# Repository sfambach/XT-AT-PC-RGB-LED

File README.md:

# XT-AT-PC-RGB-LED

**One RGB LED instead of separate power, turbo and HDD LEDs for retro PCs (XT / AT)**

| State | Colour |
|---|---|
| Power on | green |
| Turbo on | red (instead of green) |
| HDD activity | blue, overrides green and red |

It plugs into the normal mainboard headers (power LED, HDD LED, turbo LED). Two NPN transistors, five small diodes and two resistors, through-hole parts only, powered from the power LED header.

**Status: concept, simulated (ngspice).** Not built or tested yet.

## How it works

- Common anode of the RGB LED is fed from `PLED+`. The mainboard's own series resistor sets the current (optional R0 if the board has none).
- Blue cathode goes straight to `HDD-`. The open-collector HDD driver pulls it low on activity, exactly like the original HDD LED.
- Green: Q1 switches the green cathode to GND. R1 keeps Q1 on. D1 (from `HDD-`) or D2 (from `TURBO-`) pull its base down and turn green off. D4 in the emitter lifts the turn-on threshold above that one diode drop.
- Red: Q2 switches the red cathode to `TURBO-`, so red can only light while turbo is active. D3 pulls its base down on HDD activity, D5 again lifts the threshold.
- The diodes keep the two inputs apart: no input leaks into the other colour.
- `HDD+` and `TURBO+` are not used. Without a turbo connection leave out Q2, R2, D3 and D5.

Details, variants and simulation results: [docs/concept.md](docs/concept.md)

## Versions

| Version | What | Status |
|---|---|---|
| **v1** | discrete, no microcontroller, through-hole board ([hardware/v1](hardware/v1)) | simulated, board designed |
| **v2** | ATtiny84 board for an addressable LED and/or a plain RGB LED or RGB button, colours from a config file, no measuring of the headers needed ([v2/](v2/README.md), [hardware/v2](hardware/v2)) | firmware compiled, board designed |
| v3 | full SMD version | planned |

Simulation (ngspice): [sim/](sim/), transient plot `sim/three_states_tran.png`.

## History and key points

The project started as "one RGB LED for power and HDD" and grew step by step:

1. **Power + HDD with one LED.** A single diode in series with green only works with InGaN green LEDs: with a common anode the colour with the lowest forward voltage wins. One transistor solves it.
2. **Turbo added (red).** Red has about 2 V forward voltage and pulls the common anode down, so mixing colours (yellow) does not work. Result: two transistors, five diodes, HDD has priority (v1).
3. **Unknown header polarity.** Which pin of the turbo header switches is not standardised. Instead of measuring every board, v2 uses a load resistor between the two pins and treats "pins differ" as active.
4. **Microcontroller (v2).** A logic IC was rejected for v1 because the front panel has no clean 5 V. v2 accepts an extra 5 V cable and gets colours from a config file.
5. **Addressable or plain RGB?** Addressable LEDs need no resistors and can be chained; illuminated RGB buttons only exist as plain RGB. v2 has both outputs, so the power button itself can be the indicator.
6. **Boards.** v1 and v2 through-hole with the common M3 hole rule; v3 (full SMD) is planned.

Open: measurement of the front panel headers, 5 V source for v2, building and testing.

## Parts

| Ref | Part | Note |
|---|---|---|
| R1, R2 | 10 kΩ, 1/4 W | base resistors |
| R0 | 330 Ω, 1/4 W | only if `PLED+` has no series resistor on the board, otherwise bridge |
| Q1, Q2 | BC547B (BC548, 2N3904 also fine) | |
| D1–D5 | 1N4148 | |
| LED1 | RGB LED 5 mm, common anode, diffused, 4 pins | 3 mm also fine |

## License

- Hardware: [CERN-OHL-S-2.0](LICENSE)
- Firmware and tools (v2): PolyForm Noncommercial 1.0.0, see [v2/LICENSE.md](v2/LICENSE.md)
- Documentation: CC BY-SA 4.0

## Authors

- **Stefan Fambach** (SteFam) – idea and concept, review and testing – https://www.fambach.net
- **Claude** (Anthropic AI) – implementation, via Claude Code

## AI disclosure

This project is built with AI assistance. Stefan Fambach had the idea, wrote the concept and reviews and tests every change; the implementation (schematics, simulation, firmware and documentation) is written largely by Claude (Anthropic) via Claude Code.

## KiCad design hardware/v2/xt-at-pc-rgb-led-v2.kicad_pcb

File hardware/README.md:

# Hardware

Two small through-hole boards, generated with KiCad 7 from Python scripts (`generator/`) and routed with Freerouting.

| Board | Size | Content |
|---|---|---|
| [v1](v1/) | 44 × 26.5 mm | discrete: 2× BC547, 5× 1N4148, 3 resistors |
| [v2](v2/) | 42 × 40.4 mm | ATtiny84 in a DIP-14 socket, 6-pin AVR ISP, addressable and plain RGB LED output |

Each folder has the KiCad project, schematic PDF, Gerber ZIP, DRC report and top/bottom renders. 2D dimension drawings (top, front and side view) are in [drawings/](drawings/), generated from the PCB by `generator/drawing.py`.

**Status: not manufactured, not tested.** DRC: 0 unconnected pads, only silkscreen overlaps left.

## Common rules

- **Mounting:** two M3 holes (3.2 mm) on the long axis, centred, 3.5 mm from the short edges – the same on every board.
- **Connectors:** 2.54 mm pin headers. Front panel headers are 1×2 with pin 1 = `+`, pin 2 = `-`, so the usual 2-pin case cables fit.
- **LED** on a cable (1×4 header), so the board can sit anywhere behind the front panel.
- **Button / switch:** `SW IN` and `SW OUT` are connected 1:1 (pass-through only, no electronics).

## Dimensions

| Board | Outline | Holes (from top left corner) |
|---|---|---|
| v1 | 44 × 26.5 × 1.6 mm | Ø3.2 at (3.5 / 13.25) and (40.5 / 13.25) |
| v2 | 42 × 40.4 × 1.6 mm | Ø3.2 at (3.5 / 20.2) and (38.5 / 20.2) |

Resistors and diodes lie flat (7.62 mm pitch, side by side). Assumed, not measured: about 8.5 mm component height above the board (pin headers, DIP socket, TO-92) and about 3 mm leads below. Angled headers change the height.

The mounting holes sit in gaps between the parts instead of outside them, which keeps the boards narrow.

## v1 connectors

| Ref | Pins | Function |
|---|---|---|
| J1 | PLED + / − | supply (power LED header) |
| J2 | HDD + / − | only `−` is used |
| J3 | TURBO + / − | only `−` is used |
| J4 | A R G B | RGB LED, common anode |
| J5 / J6 | SW IN / SW OUT | pass-through |

R0 only if `PLED+` has no series resistor on the mainboard, otherwise a wire bridge.

## v2 connectors

| Ref | Pins | Function |
|---|---|---|
| J1 | +5V GND | supply (speaker header / floppy connector, to be checked) |
| J2 / J3 | HDD, TURBO | any polarity, R1/R4 4.7 kΩ load between the pins |
| J4 / J5 | SW IN / SW OUT | pass-through |
| J6 | 5V DATA GND | addressable LED |
| J7 | COM R G B | plain RGB LED / RGB button, R9–R11 only when used |
| JP1 | A – COM – K | COM to +5 V (common anode) or GND (common cathode) |
| J8 | ISP | standard 6-pin AVR ISP (MISO VCC / SCK MOSI / RST GND) |

The ATtiny84 can also be programmed in a socket programmer (XGecu T48). MOSI is shared with the blue PWM output; the blue LED may flicker while programming.

## Rebuild

```
cd generator
FREEROUTING=/path/to/freerouting-1.9.0.jar sh build.sh v1
sh outputs.sh v1
```

Freerouting is not deterministic; if the DRC reports unconnected pads, run `build.sh` again.

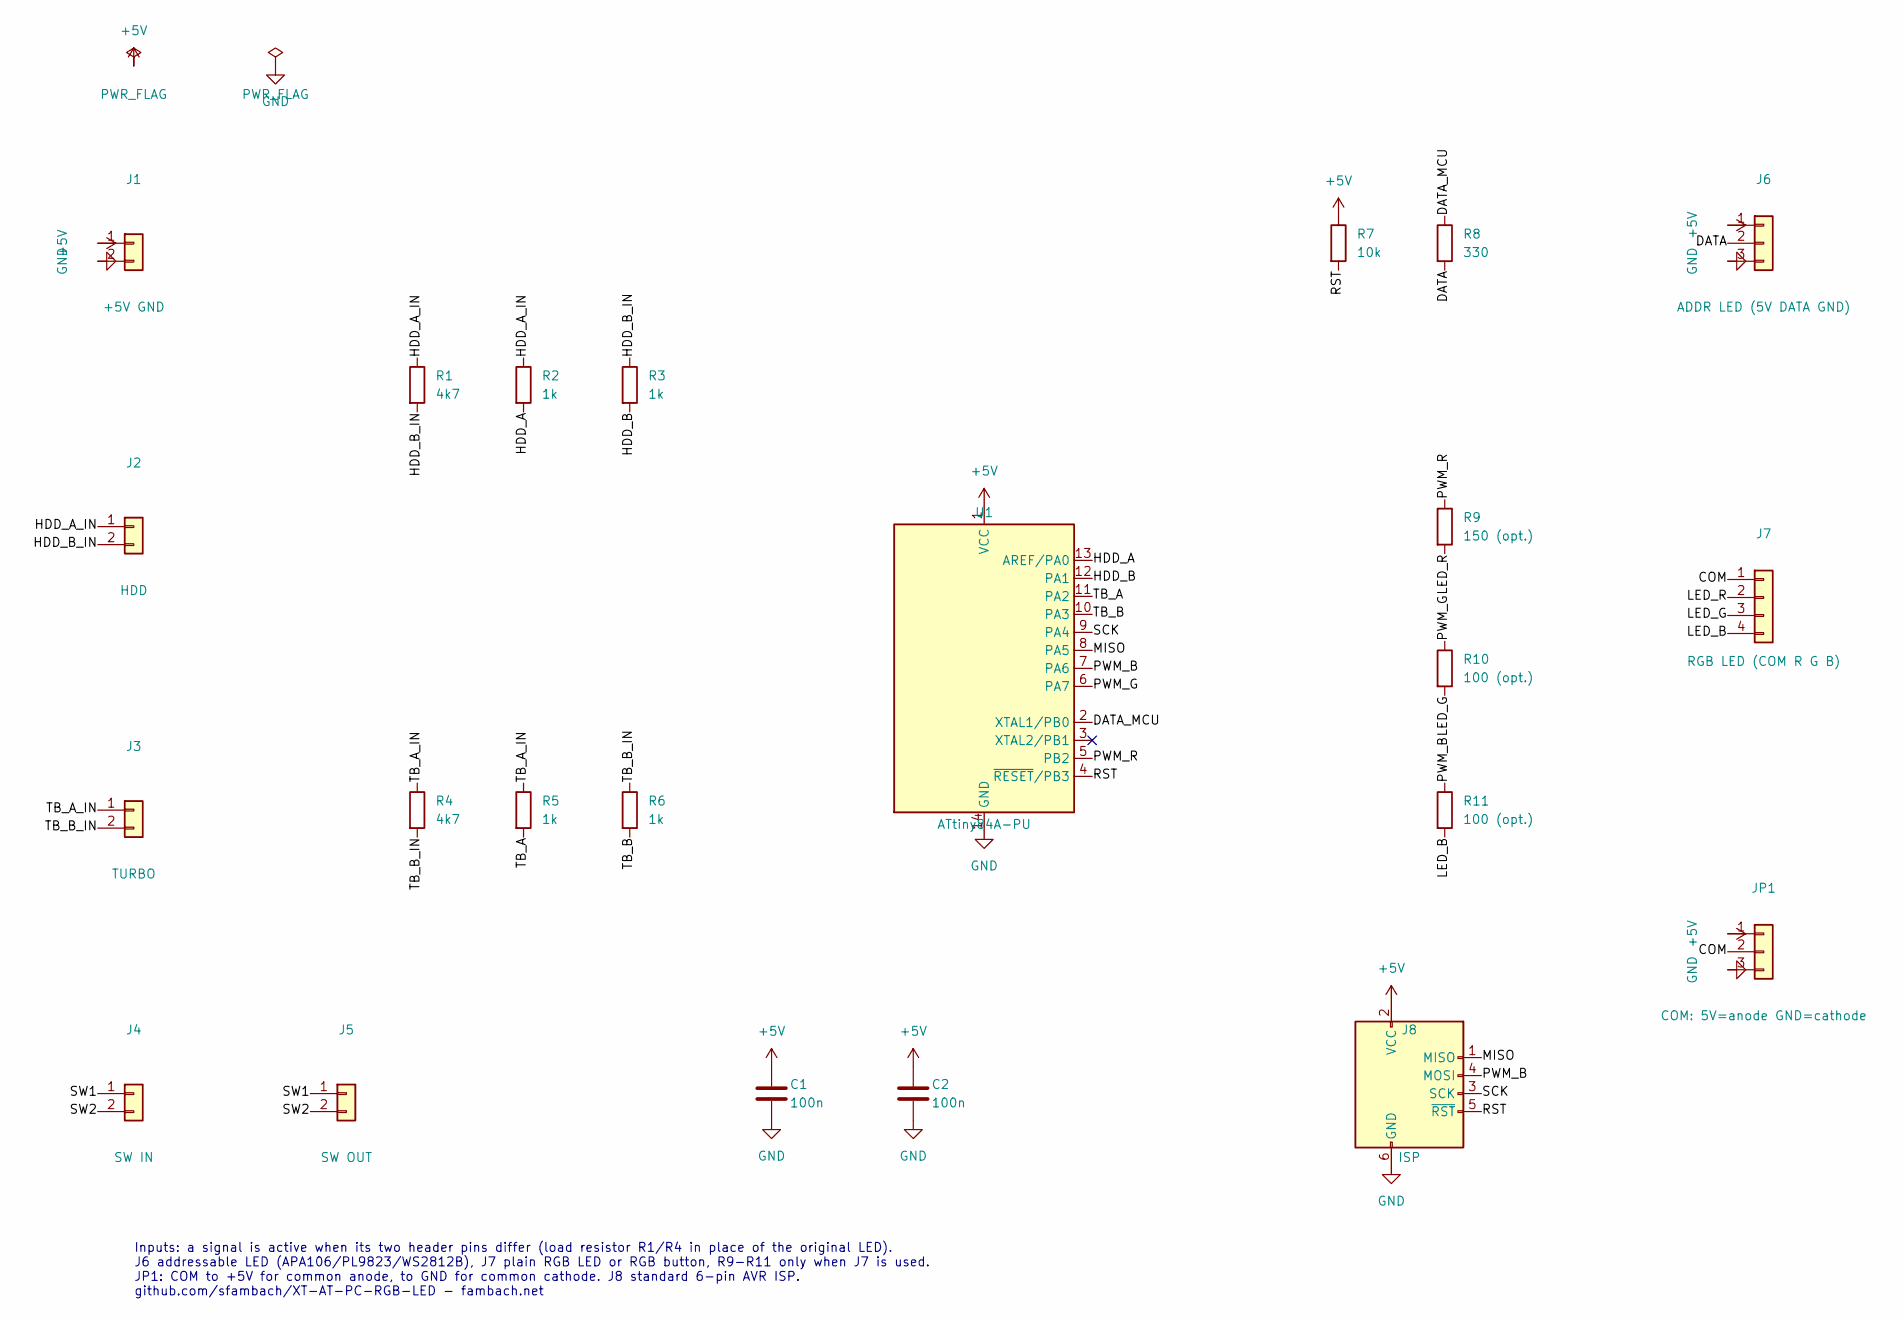
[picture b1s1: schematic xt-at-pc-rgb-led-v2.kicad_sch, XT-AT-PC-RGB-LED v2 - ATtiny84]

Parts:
C1, C2: 100n; C_Disc_D3.0mm_W1.6mm_P2.50mm
J1: +5V GND; PinHeader_1x02_P2.54mm_Vertical
J2: HDD; PinHeader_1x02_P2.54mm_Vertical
J3: TURBO; PinHeader_1x02_P2.54mm_Vertical
J4: SW IN; PinHeader_1x02_P2.54mm_Vertical
J5: SW OUT; PinHeader_1x02_P2.54mm_Vertical
J6: ADDR LED (5V DATA GND); PinHeader_1x03_P2.54mm_Vertical
J7: RGB LED (COM R G B); PinHeader_1x04_P2.54mm_Vertical
J8: ISP; PinHeader_2x03_P2.54mm_Vertical
JP1: COM: 5V=anode GND=cathode; PinHeader_1x03_P2.54mm_Vertical
R1, R4: 4k7; R_Axial_DIN0207_L6.3mm_D2.5mm_P7.62mm_Horizontal
R2, R3, R5, R6: 1k; R_Axial_DIN0207_L6.3mm_D2.5mm_P7.62mm_Horizontal
R7: 10k; R_Axial_DIN0207_L6.3mm_D2.5mm_P7.62mm_Horizontal
R8: 330; R_Axial_DIN0207_L6.3mm_D2.5mm_P7.62mm_Horizontal
R9: 150 (opt.); R_Axial_DIN0207_L6.3mm_D2.5mm_P7.62mm_Horizontal
R10, R11: 100 (opt.); R_Axial_DIN0207_L6.3mm_D2.5mm_P7.62mm_Horizontal
U1: ATtiny84A-PU; DIP-14_W7.62mm_Socket

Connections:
+5V: C1.1, C2.1, J1.1, J6.1, J8.2 (VCC), JP1.1, R7.1, U1.1 (VCC)
/COM: J7.1, JP1.2
/DATA: J6.2, R8.2
/DATA_MCU: R8.1, U1.2 (XTAL1/PB0)
/HDD_A: R2.2, U1.13 (AREF/PA0)
/HDD_A_IN: J2.1, R1.1, R2.1
/HDD_B: R3.2, U1.12 (PA1)
/HDD_B_IN: J2.2, R1.2, R3.1
/LED_B: J7.4, R11.2
/LED_G: J7.3, R10.2
/LED_R: J7.2, R9.2
/MISO: J8.1 (MISO), U1.8 (PA5)
/PWM_B: J8.4 (MOSI), R11.1, U1.7 (PA6)
/PWM_G: R10.1, U1.6 (PA7)
/PWM_R: R9.1, U1.5 (PB2)
/RST: J8.5 (~RST), R7.2, U1.4 (~RESET/PB3)
/SCK: J8.3 (SCK), U1.9 (PA4)
/SW1: J4.1, J5.1
/SW2: J4.2, J5.2
/TB_A: R5.2, U1.11 (PA2)
/TB_A_IN: J3.1, R4.1, R5.1
/TB_B: R6.2, U1.10 (PA3)
/TB_B_IN: J3.2, R4.2, R6.1
GND: C1.2, C2.2, J1.2, J6.3, J8.6 (GND), JP1.3, U1.14 (GND)

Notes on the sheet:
Inputs: a signal is active when its two header pins differ (load resistor R1/R4 in place of the original LED). J6 addressable LED (APA106/PL9823/WS2812B), J7 plain RGB LED or RGB button, R9-R11 only when J7 is used. JP1: COM to +5V for common anode, to GND for common cathode. J8 standard 6-pin AVR 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

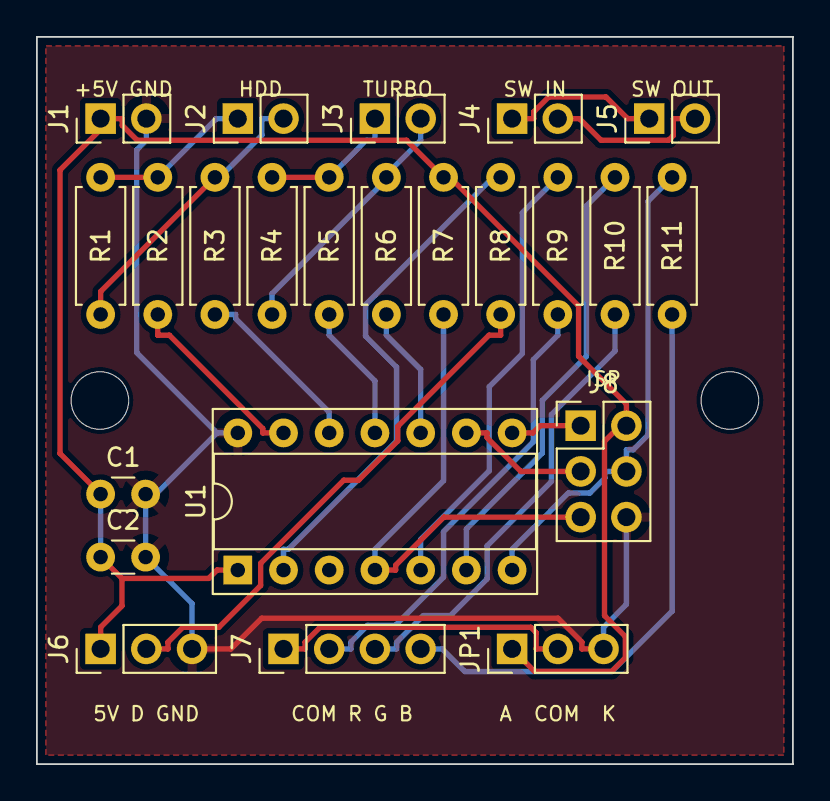
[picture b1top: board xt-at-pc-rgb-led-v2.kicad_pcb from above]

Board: 2 copper layers, 42.0 x 40.4 mm, 25 parts (0 on the bottom side), 24 nets.

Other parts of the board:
H1, H2: M3; MountingHole_3.2mm_M3

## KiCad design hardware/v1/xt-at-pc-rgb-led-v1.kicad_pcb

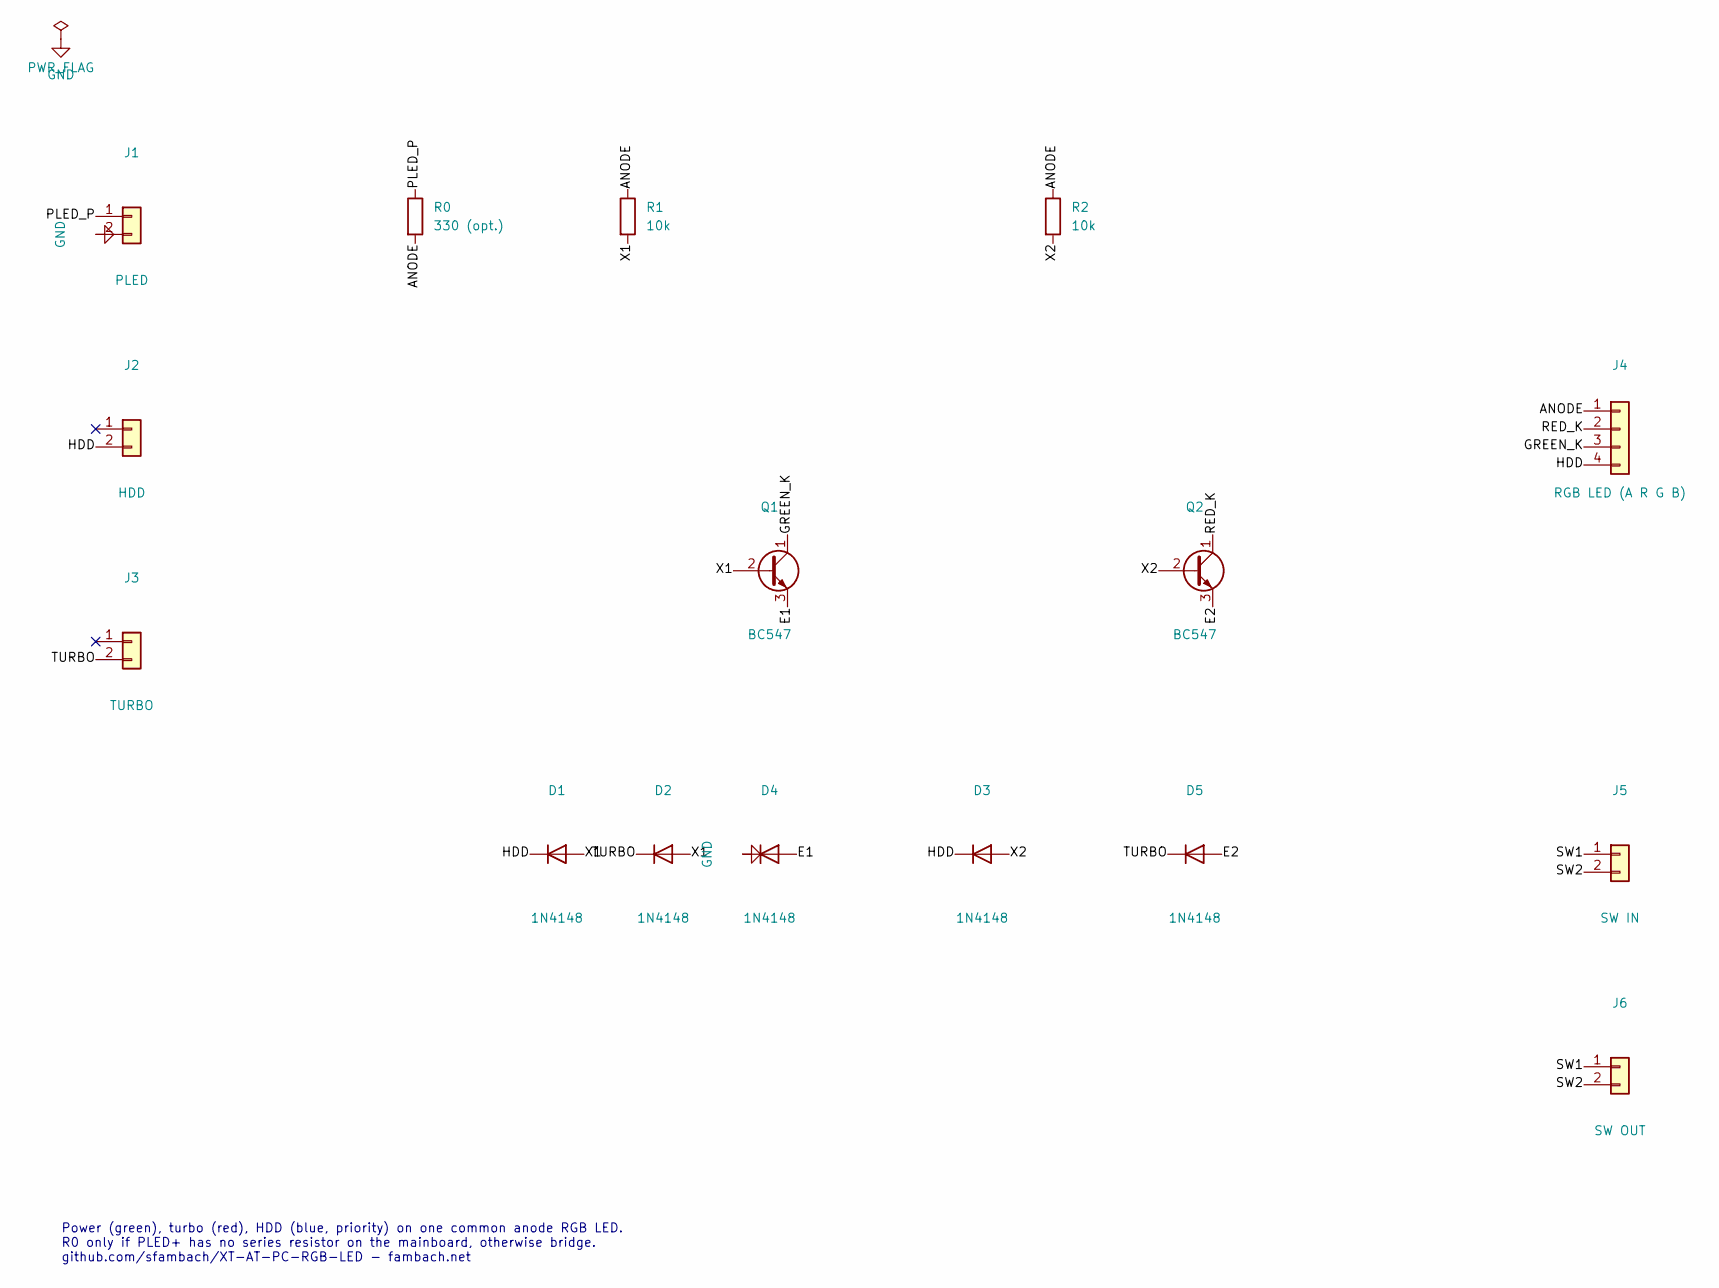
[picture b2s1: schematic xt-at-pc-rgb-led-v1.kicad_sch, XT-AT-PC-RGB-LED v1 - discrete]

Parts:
D1, D2, D3, D4, D5: 1N4148; D_DO-35_SOD27_P7.62mm_Horizontal
J1: PLED; PinHeader_1x02_P2.54mm_Vertical
J2: HDD; PinHeader_1x02_P2.54mm_Vertical
J3: TURBO; PinHeader_1x02_P2.54mm_Vertical
J4: RGB LED (A R G B); PinHeader_1x04_P2.54mm_Vertical
J5: SW IN; PinHeader_1x02_P2.54mm_Vertical
J6: SW OUT; PinHeader_1x02_P2.54mm_Vertical
Q1, Q2: BC547; TO-92_Inline_Wide
R0: 330 (opt.); R_Axial_DIN0207_L6.3mm_D2.5mm_P7.62mm_Horizontal
R1, R2: 10k; R_Axial_DIN0207_L6.3mm_D2.5mm_P7.62mm_Horizontal

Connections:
/ANODE: J4.1, R0.2, R1.1, R2.1
/E1: D4.2 (A), Q1.3 (E)
/E2: D5.2 (A), Q2.3 (E)
/GREEN_K: J4.3, Q1.1 (C)
/HDD: D1.1 (K), D3.1 (K), J2.2, J4.4
/PLED_P: J1.1, R0.1
/RED_K: J4.2, Q2.1 (C)
/SW1: J5.1, J6.1
/SW2: J5.2, J6.2
/TURBO: D2.1 (K), D5.1 (K), J3.2
/X1: D1.2 (A), D2.2 (A), Q1.2 (B), R1.2
/X2: D3.2 (A), Q2.2 (B), R2.2
GND: D4.1 (K), J1.2

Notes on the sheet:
Power (green), turbo (red), HDD (blue, priority) on one common anode RGB LED. R0 only if PLED+ has no series resistor on the mainboard, otherwise bridge. github.com/sfambach/XT-AT-PC-RGB-LED - fambach.net

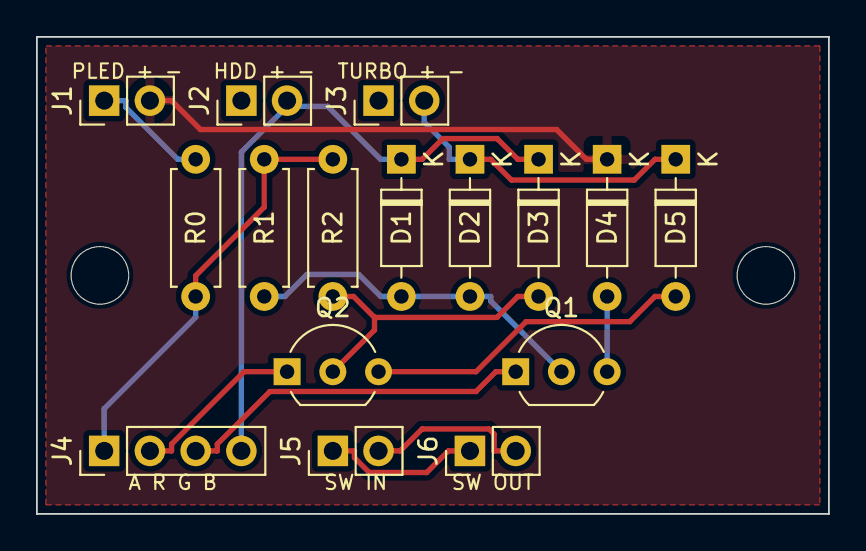
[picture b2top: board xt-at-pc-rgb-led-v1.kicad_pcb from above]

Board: 2 copper layers, 44.0 x 26.5 mm, 18 parts (0 on the bottom side), 13 nets.

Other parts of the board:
H1, H2: M3; MountingHole_3.2mm_M3

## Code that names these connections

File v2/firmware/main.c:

/*
 * XT-AT-PC-RGB-LED v2 - one RGB LED for power, turbo and HDD
 * Copyright (C) 2026 Stefan Fambach (SteFam), https://www.fambach.net
 * License: PolyForm Noncommercial 1.0.0, see ../LICENSE.md
 *
 * Internal oscillator: ATtiny84 / ATtiny85 @ 8 MHz, ATtiny13A @ 9.6 MHz.
 *
 * ATtiny85 / ATtiny13A (addressable LED only)
 *   PB0 LED data   PB1/PB2 HDD header pins A/B   PB3/PB4 TURBO header pins A/B
 *
 * ATtiny84 (addressable LED and plain RGB LED at the same time)
 *   PB0 LED data   PA0/PA1 HDD header pins A/B   PA2/PA3 TURBO header pins A/B
 *   PB2 (OC0A) red   PA7 (OC0B) green   PA6 (OC1A) blue
 *
 * Each header gets a load resistor between its two pins. A signal is active
 * when its two pins differ, so neither the header polarity nor the switching
 * side (low or high) has to be known in advance.
 */
#include <avr/io.h>
#include <avr/eeprom.h>
#include <avr/interrupt.h>
#include <util/delay.h>
#include "config.h"

#define LED_BIT    _BV(PB0)
#define REFRESH_MS 500

#if defined(__AVR_ATtiny84__) || defined(__AVR_ATtiny84A__)
#define HAS_RGB_OUTPUT 1
#define INPUT_PIN  PINA
#define INPUT_PORT PORTA
#define HDD_A PA0
#define HDD_B PA1
#define TURBO_A PA2
#define TURBO_B PA3
#else
#define HAS_RGB_OUTPUT 0
#define INPUT_PIN  PINB
#define INPUT_PORT PORTB
#define HDD_A PB1
#define HDD_B PB2
#define TURBO_A PB3
#define TURBO_B PB4
#endif
#define INPUTS (_BV(HDD_A) | _BV(HDD_B) | _BV(TURBO_A) | _BV(TURBO_B))

static struct config cfg;

/* 11 cycles per bit: high 3 cycles for 0, 7 cycles for 1 (8 / 9.6 MHz). */
static void send_byte(uint8_t value, uint8_t hi, uint8_t lo)
{
    uint8_t count = 8;
    __asm__ volatile(
        "1:                 \n\t"
        "out  %[port], %[hi]\n\t"
        "nop                \n\t"
        "sbrs %[val], 7     \n\t"
        "out  %[port], %[lo]\n\t"
        "lsl  %[val]        \n\t"
        "nop                \n\t"
        "nop                \n\t"
        "out  %[port], %[lo]\n\t"
        "dec  %[cnt]        \n\t"
        "brne 1b            \n\t"
        : [val] "+r"(value), [cnt] "+r"(count)
        : [port] "I"(_SFR_IO_ADDR(PORTB)), [hi] "r"(hi), [lo] "r"(lo));
}

static uint8_t scale(uint8_t channel)
{
    return (uint16_t)channel * (cfg.brightness + 1) >> 8;
}

#if HAS_RGB_OUTPUT
/*
 * Hardware PWM, 8 bit, ~3.9 kHz. Common anode is driven inverted (low = on).
 * A channel at 0 is disconnected from the timer and held at its off level,
 * because fast PWM never reaches a duty of exactly 0.
 */
static void pwm_init(void)
{
    if (cfg.rgb_output == RGB_NONE)
        return;
    if (cfg.rgb_output == RGB_COMMON_ANODE) {
        PORTB |= _BV(PB2);
        PORTA |= _BV(PA7) | _BV(PA6);
    }
    DDRB |= _BV(PB2);
    DDRA |= _BV(PA7) | _BV(PA6);
    TCCR0A = _BV(WGM01) | _BV(WGM00);
    TCCR0B = _BV(CS01);
    TCCR1A = _BV(WGM10);
    TCCR1B = _BV(WGM12) | _BV(CS11);
}

static uint8_t com_bits(uint8_t value, uint8_t com1, uint8_t com0)
{
    if (value == 0)
        return 0;
    return cfg.rgb_output == RGB_COMMON_ANODE ? (com1 | com0) : com1;
}

static void pwm_show(uint8_t r, uint8_t g, uint8_t b)
{
    if (cfg.rgb_output == RGB_NONE)
        return;
    OCR0A = r - 1;
    OCR0B = g - 1;
    OCR1A = b - 1;
    TCCR0A = _BV(WGM01) | _BV(WGM00) |
             com_bits(r, _BV(COM0A1), _BV(COM0A0)) |
             com_bits(g, _BV(COM0B1), _BV(COM0B0));
    TCCR1A = _BV(WGM10) | com_bits(b, _BV(COM1A1), _BV(COM1A0));
}
#endif

static void show(const uint8_t rgb[3])
{
    uint8_t r = scale(rgb[0]), g = scale(rgb[1]), b = scale(rgb[2]);
    uint8_t first = cfg.order == ORDER_RGB ? r : g;
    uint8_t second = cfg.order == ORDER_RGB ? g : r;
    uint8_t hi = PORTB | LED_BIT, lo = PORTB & ~LED_BIT;

    cli();
    for (uint8_t i = 0; i < cfg.led_count; i++) {
        send_byte(first, hi, lo);
        send_byte(second, hi, lo);
        send_byte(b, hi, lo);
    }
    sei();
#if HAS_RGB_OUTPUT
    pwm_show(r, g, b);
#endif
    _delay_us(80); /* latch */
}

static void load_config(void)
{
    static const struct config defaults = CONFIG_DEFAULTS;

    eeprom_read_block(&cfg, 0, sizeof cfg);
    if (cfg.magic != CONFIG_MAGIC || cfg.version != CONFIG_VERSION || cfg.led_count == 0)
        cfg = defaults;
}

int main(void)
{
    uint8_t mixed[3], current[3] = { 1, 1, 1 };
    const uint8_t *colour;
    uint16_t hdd_hold = 0, refresh = 0;

    DDRB = LED_BIT;
    INPUT_PORT = INPUTS; /* pull-ups keep unconnected header pairs equal */
    load_config();
#if HAS_RGB_OUTPUT
    pwm_init();
#endif

    for (uint8_t i = 0; i < 3; i++) {
        uint16_t sum = cfg.power[i] + cfg.turbo[i];
        mixed[i] = sum > 255 ? 255 : sum;
    }
    _delay_ms(50);

    for (;;) {
        uint8_t pins = INPUT_PIN;
        uint8_t hdd = ((pins >> HDD_A) ^ (pins >> HDD_B)) & 1;
        uint8_t turbo = ((pins >> TURBO_A) ^ (pins >> TURBO_B)) & 1;

        /* short HDD pulses would be invisible, stretch them */
        if (hdd)
            hdd_hold = cfg.hdd_hold * 10;
        else if (hdd_hold)
            hdd_hold--;

        if (hdd_hold || hdd)
            colour = cfg.hdd;
        else if (turbo)
            colour = cfg.turbo_mode == TURBO_MIX ? mixed : cfg.turbo;
        else
            colour = cfg.power;

        if (colour[0] != current[0] || colour[1] != current[1] ||
            colour[2] != current[2] || ++refresh >= REFRESH_MS) {
            show(colour);
            current[0] = colour[0];
            current[1] = colour[1];
            current[2] = colour[2];
            refresh = 0;
        }
        _delay_ms(1);
    }
}

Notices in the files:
hardware/v1/xt-at-pc-rgb-led-v1.kicad_pcb:
XT-AT-PC-RGB-LED v1 - fambach.net - CERN-OHL-S-2.0
hardware/v2/xt-at-pc-rgb-led-v2.kicad_pcb:
XT-AT-PC-RGB-LED v2 - fambach.net - CERN-OHL-S-2.0
